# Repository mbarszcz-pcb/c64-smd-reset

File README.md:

# c64-smd-reset
Unstoppable Reset Circuit PCB using SMD Parts

Based on the unstoppable reset on C64 wiki https://www.c64-wiki.com/wiki/Reset_Button, here is a small 1206 SMD PCB that mounts directly on the back of a pushbutton switch

## BOM

All SMD parts are 1202 size.  Feel free to use any brand, but example manufacturer parts have been provided below

| Description        | Qty    | Value                               | Example Manufacturer Part #     |
| ------------------ |-------:| ------------------------------------|---------------------------------|
| Pushbutton Switch  | 1      | Momentary SPST, 5.31mm leg spacing  | C&K 8531SZQE2                   |
| SOD-123  Diode     | 1      | 1N4148                              | Diodes Incorporated 1N4148W-7-F |
| 1206 10K Resistor  | 1      | 10K                                 | Vishay CRCW120610K0FKEAC        |
| 1206 12K Resistor  | 1      | 12K                                 | Vishay CRCW120612K0FKEAC        |
| 1206 10uF Capacitor| 2      | 10uF 10% MLCC                       | Taiyo Yuden EMK316BJ106KD       |

## Build notes
The switch should be inserted through the PCB and soldered on the front side (the side with the SMD components).  This will allow the PCB to hang off the back of the switch when it is mounted in the case.  Throughole spacing above the switch is standard 0.1" so a header can be installed for quick disconnect, or wired directly if you prefer.

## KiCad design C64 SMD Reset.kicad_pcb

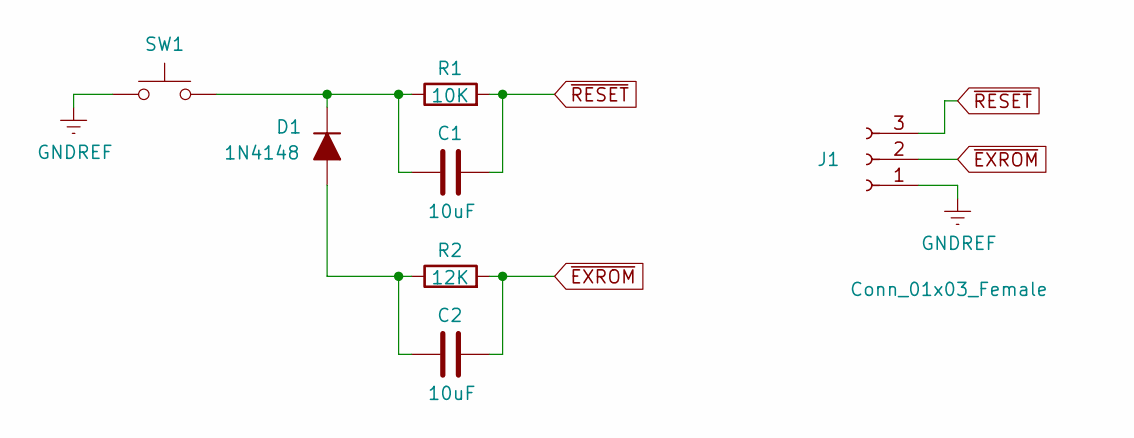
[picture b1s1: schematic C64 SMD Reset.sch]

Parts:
C1, C2: 10uF; C_1206_3216Metric_Pad1.42x1.75mm_HandSolder
D1: 1N4148; D_SOD-123-diodemarkonsilk
J1: Conn_01x03_Female; PinHeader_1x03_P2.54mm_Vertical-NoSilk
R1: 10K; R_1206_3216Metric_Pad1.42x1.75mm_HandSolder
R2: 12K; R_1206_3216Metric_Pad1.42x1.75mm_HandSolder
SW1: SW_Push; PushbuttonSW_TH_8531SZQE2

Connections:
GNDREF: J1.1, SW1.2
unnamed: C1.1, D1.1 (K), R1.1, SW1.1
unnamed: C2.1, D1.2 (A), R2.1
~EXROM: C2.2, J1.2, R2.2
~RESET: C1.2, J1.3, R1.2

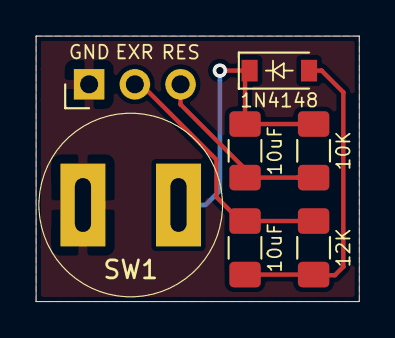
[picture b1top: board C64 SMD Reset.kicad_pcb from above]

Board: 2 copper layers, 18.0 x 14.7 mm, 7 parts (0 on the bottom side), 5 nets.
